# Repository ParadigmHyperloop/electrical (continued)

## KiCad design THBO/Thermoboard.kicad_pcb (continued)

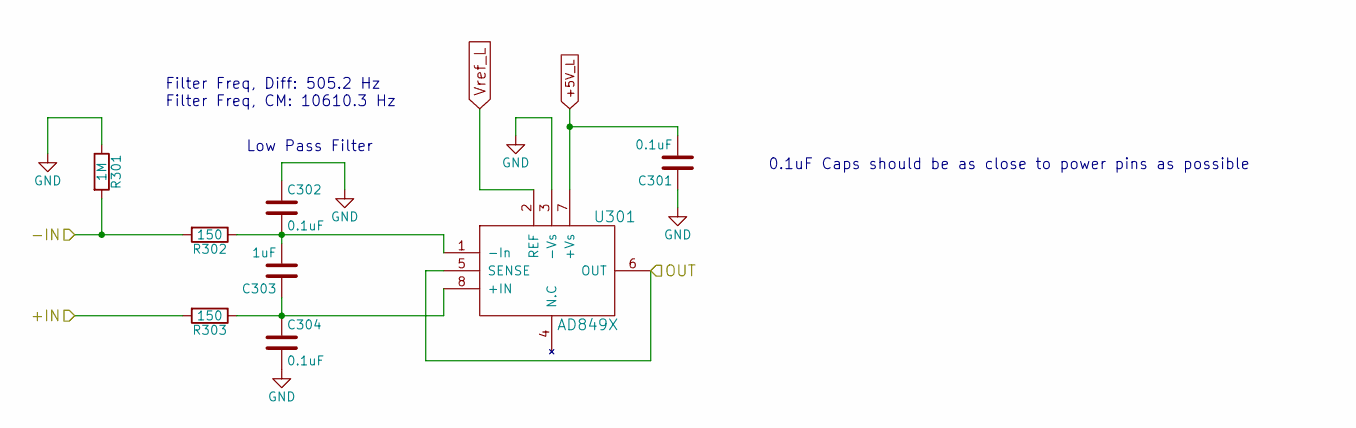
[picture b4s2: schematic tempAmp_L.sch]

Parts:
C201, C202, C204: 0.1uF; C_0603_HandSoldering; Digikey P/N 311-1088-1-ND
C203: 1uF; C_0603_HandSoldering; Digikey P/N 1276-1946-1-ND
R201: 1M; R_0603_HandSoldering; Digikey P/N 311-1.00MHRCT-ND
R202, R203: 150; R_0603_HandSoldering; Digikey P/N 311-150HRCT-ND
U201: AD849X; MSOP-8_3x3mm_Pitch0.65mm; Digikey P/N AD8497ARMZ-ND

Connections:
+5V_L: C201.2, U201.7 (+Vs); also elsewhere on the board
/THERMO_OUPUT_1: U201.5 (SENSE), U201.6 (OUT); also elsewhere on the board
/Thermocouple Amplifier -- 1/+IN: R203.2; also elsewhere on the board
/Thermocouple Amplifier -- 1/-IN: R201.2, R202.2; also elsewhere on the board
GND: C201.1, C202.1, C204.2, R201.1, U201.3 (-Vs); also elsewhere on the board
unnamed: C202.2, C203.2, R202.1, U201.1 (-In)
unnamed: C203.1, C204.1, R203.1, U201.8 (+IN)
Vref_L: U201.2 (REF); also elsewhere on the board

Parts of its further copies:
C301, C302, C304, C401, C402, C404, C501, C502, C504, C601, C602, C604, C701, C702, C704, C801, C802, C804, C901, C902, C904, C1001, C1002, C1004, C1101, C1102, C1104, C1201, C1202, C1204, C1301, C1302, C1304, C1401, C1402, C1404, C1501, C1502, C1504, C1601, C1602, C1604, C1701, C1702, C1704, C1801, C1802, C1804, C1901, C1902, C1904, C2001, C2002, C2004, C2101, C2102, C2104, C2201, C2202, C2204, C2301, C2302, C2304, C2401, C2402, C2404, C2501, C2502, C2504, C2601, C2602, C2604, C2701, C2702, C2704, C2801, C2802, C2804, C2901, C2902, C2904, C3001, C3002, C3004, C3101, C3102, C3104, C3201, C3202, C3204, C3301, C3302, C3304: 0.1uF; C_0603_HandSoldering; Digikey P/N 311-1088-1-ND
C303, C403, C503, C603, C703, C803, C903, C1003, C1103, C1203, C1303, C1403, C1503, C1603, C1703, C1803, C1903, C2003, C2103, C2203, C2303, C2403, C2503, C2603, C2703, C2803, C2903, C3003, C3103, C3203, C3303: 1uF; C_0603_HandSoldering; Digikey P/N 1276-1946-1-ND
R301, R401, R501, R601, R701, R801, R901, R1001, R1101, R1201, R1301, R1401, R1501, R1601, R1701, R1801, R1901, R2001, R2101, R2201, R2301, R2401, R2501, R2601, R2701, R2801, R2901, R3001, R3101, R3201, R3301: 1M; R_0603_HandSoldering; Digikey P/N 311-1.00MHRCT-ND
R302, R303, R402, R403, R502, R503, R602, R603, R702, R703, R802, R803, R902, R903, R1002, R1003, R1102, R1103, R1202, R1203, R1302, R1303, R1402, R1403, R1502, R1503, R1602, R1603, R1702, R1703, R1802, R1803, R1902, R1903, R2002, R2003, R2102, R2103, R2202, R2203, R2302, R2303, R2402, R2403, R2502, R2503, R2602, R2603, R2702, R2703, R2802, R2803, R2902, R2903, R3002, R3003, R3102, R3103, R3202, R3203, R3302, R3303: 150; R_0603_HandSoldering; Digikey P/N 311-150HRCT-ND
U301, U401, U501, U601, U701, U801, U901, U1001, U1101, U1201, U1301, U1401, U1501, U1601, U1701, U1801, U1901, U2001, U2101, U2201, U2301, U2401, U2501, U2601, U2701, U2801, U2901, U3001, U3101, U3201, U3301: AD849X; MSOP-8_3x3mm_Pitch0.65mm; Digikey P/N AD8497ARMZ-ND

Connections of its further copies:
+5V_L: C301.2, C401.2, C501.2, C601.2, C701.2, C801.2, C901.2, C1001.2, C1101.2, C1201.2, C1301.2, C1401.2, C1501.2, C1601.2, C1701.2, U301.7 (+Vs), U401.7 (+Vs), U501.7 (+Vs), U601.7 (+Vs), U701.7 (+Vs), U801.7 (+Vs), U901.7 (+Vs), U1001.7 (+Vs), U1101.7 (+Vs), U1201.7 (+Vs), U1301.7 (+Vs), U1401.7 (+Vs), U1501.7 (+Vs), U1601.7 (+Vs), U1701.7 (+Vs); also elsewhere on the board
+5V_R: C1801.2, C1901.2, C2001.2, C2101.2, C2201.2, C2301.2, C2401.2, C2501.2, C2601.2, C2701.2, C2801.2, C2901.2, C3001.2, C3101.2, C3201.2, C3301.2, U1801.7 (+Vs), U1901.7 (+Vs), U2001.7 (+Vs), U2101.7 (+Vs), U2201.7 (+Vs), U2301.7 (+Vs), U2401.7 (+Vs), U2501.7 (+Vs), U2601.7 (+Vs), U2701.7 (+Vs), U2801.7 (+Vs), U2901.7 (+Vs), U3001.7 (+Vs), U3101.7 (+Vs), U3201.7 (+Vs), U3301.7 (+Vs); also elsewhere on the board
/THERMO_OUPUT_2: U301.5 (SENSE), U301.6 (OUT); also elsewhere on the board
/THERMO_OUPUT_3: U401.5 (SENSE), U401.6 (OUT); also elsewhere on the board
/THERMO_OUPUT_4: U501.5 (SENSE), U501.6 (OUT); also elsewhere on the board
/THERMO_OUPUT_5: U601.5 (SENSE), U601.6 (OUT); also elsewhere on the board
/THERMO_OUPUT_6: U701.5 (SENSE), U701.6 (OUT); also elsewhere on the board
/THERMO_OUPUT_7: U801.5 (SENSE), U801.6 (OUT); also elsewhere on the board
/THERMO_OUPUT_8: U901.5 (SENSE), U901.6 (OUT); also elsewhere on the board
/THERMO_OUPUT_9: U1001.5 (SENSE), U1001.6 (OUT); also elsewhere on the board
/THERMO_OUPUT_10: U1101.5 (SENSE), U1101.6 (OUT); also elsewhere on the board
/THERMO_OUPUT_11: U1201.5 (SENSE), U1201.6 (OUT); also elsewhere on the board
/THERMO_OUPUT_12: U1301.5 (SENSE), U1301.6 (OUT); also elsewhere on the board
/THERMO_OUPUT_13: U1401.5 (SENSE), U1401.6 (OUT); also elsewhere on the board
/THERMO_OUPUT_14: U1501.5 (SENSE), U1501.6 (OUT); also elsewhere on the board
/THERMO_OUPUT_15: U1601.5 (SENSE), U1601.6 (OUT); also elsewhere on the board
/THERMO_OUPUT_16: U1701.5 (SENSE), U1701.6 (OUT); also elsewhere on the board
/THERMO_OUPUT_17: U1801.5 (SENSE), U1801.6 (OUT); also elsewhere on the board
/THERMO_OUPUT_18: U1901.5 (SENSE), U1901.6 (OUT); also elsewhere on the board
/THERMO_OUPUT_19: U2001.5 (SENSE), U2001.6 (OUT); also elsewhere on the board
/THERMO_OUPUT_20: U2101.5 (SENSE), U2101.6 (OUT); also elsewhere on the board
/THERMO_OUPUT_21: U2201.5 (SENSE), U2201.6 (OUT); also elsewhere on the board
/THERMO_OUPUT_22: U2301.5 (SENSE), U2301.6 (OUT); also elsewhere on the board
/THERMO_OUPUT_23: U2401.5 (SENSE), U2401.6 (OUT); also elsewhere on the board
/THERMO_OUPUT_24: U2501.5 (SENSE), U2501.6 (OUT); also elsewhere on the board
/THERMO_OUPUT_25: U2601.5 (SENSE), U2601.6 (OUT); also elsewhere on the board
/THERMO_OUPUT_26: U2701.5 (SENSE), U2701.6 (OUT); also elsewhere on the board
/THERMO_OUPUT_27: U2801.5 (SENSE), U2801.6 (OUT); also elsewhere on the board
/THERMO_OUPUT_28: U2901.5 (SENSE), U2901.6 (OUT); also elsewhere on the board
/THERMO_OUPUT_29: U3001.5 (SENSE), U3001.6 (OUT); also elsewhere on the board
/THERMO_OUPUT_30: U3101.5 (SENSE), U3101.6 (OUT); also elsewhere on the board
/THERMO_OUPUT_31: U3201.5 (SENSE), U3201.6 (OUT); also elsewhere on the board
/THERMO_OUPUT_32: U3301.5 (SENSE), U3301.6 (OUT); also elsewhere on the board
/Thermocouple Amplifier -- 2/+IN: R303.2; also elsewhere on the board
/Thermocouple Amplifier -- 2/-IN: R301.2, R302.2; also elsewhere on the board
/Thermocouple Amplifier -- 3/+IN: R403.2; also elsewhere on the board
/Thermocouple Amplifier -- 3/-IN: R401.2, R402.2; also elsewhere on the board
/Thermocouple Amplifier -- 4/+IN: R503.2; also elsewhere on the board
/Thermocouple Amplifier -- 4/-IN: R501.2, R502.2; also elsewhere on the board
/Thermocouple Amplifier -- 5/+IN: R603.2; also elsewhere on the board
/Thermocouple Amplifier -- 5/-IN: R601.2, R602.2; also elsewhere on the board
/Thermocouple Amplifier -- 6/+IN: R703.2; also elsewhere on the board
/Thermocouple Amplifier -- 6/-IN: R701.2, R702.2; also elsewhere on the board
/Thermocouple Amplifier -- 7/+IN: R803.2; also elsewhere on the board
/Thermocouple Amplifier -- 7/-IN: R801.2, R802.2; also elsewhere on the board
/Thermocouple Amplifier -- 8/+IN: R903.2; also elsewhere on the board
/Thermocouple Amplifier -- 8/-IN: R901.2, R902.2; also elsewhere on the board
/Thermocouple Amplifier -- 9/+IN: R1003.2; also elsewhere on the board
/Thermocouple Amplifier -- 9/-IN: R1001.2, R1002.2; also elsewhere on the board
/Thermocouple Amplifier -- 10/+IN: R1103.2; also elsewhere on the board
/Thermocouple Amplifier -- 10/-IN: R1101.2, R1102.2; also elsewhere on the board
/Thermocouple Amplifier -- 11/+IN: R1203.2; also elsewhere on the board
/Thermocouple Amplifier -- 11/-IN: R1201.2, R1202.2; also elsewhere on the board
/Thermocouple Amplifier -- 12/+IN: R1303.2; also elsewhere on the board
/Thermocouple Amplifier -- 12/-IN: R1301.2, R1302.2; also elsewhere on the board
/Thermocouple Amplifier -- 13/+IN: R1403.2; also elsewhere on the board
/Thermocouple Amplifier -- 13/-IN: R1401.2, R1402.2; also elsewhere on the board
/Thermocouple Amplifier -- 14/+IN: R1503.2; also elsewhere on the board
/Thermocouple Amplifier -- 14/-IN: R1501.2, R1502.2; also elsewhere on the board
/Thermocouple Amplifier -- 15/+IN: R1603.2; also elsewhere on the board
/Thermocouple Amplifier -- 15/-IN: R1601.2, R1602.2; also elsewhere on the board
/Thermocouple Amplifier -- 16/+IN: R1703.2; also elsewhere on the board
/Thermocouple Amplifier -- 16/-IN: R1701.2, R1702.2; also elsewhere on the board
/Thermocouple Amplifier -- 17/+IN: R1803.2; also elsewhere on the board
/Thermocouple Amplifier -- 17/-IN: R1801.2, R1802.2; also elsewhere on the board
/Thermocouple Amplifier -- 18/+IN: R1903.2; also elsewhere on the board
/Thermocouple Amplifier -- 18/-IN: R1901.2, R1902.2; also elsewhere on the board
/Thermocouple Amplifier -- 19/+IN: R2003.2; also elsewhere on the board
/Thermocouple Amplifier -- 19/-IN: R2001.2, R2002.2; also elsewhere on the board
/Thermocouple Amplifier -- 20/+IN: R2103.2; also elsewhere on the board
/Thermocouple Amplifier -- 20/-IN: R2101.2, R2102.2; also elsewhere on the board
/Thermocouple Amplifier -- 21/+IN: R2203.2; also elsewhere on the board
/Thermocouple Amplifier -- 21/-IN: R2201.2, R2202.2; also elsewhere on the board
/Thermocouple Amplifier -- 22/+IN: R2303.2; also elsewhere on the board
/Thermocouple Amplifier -- 22/-IN: R2301.2, R2302.2; also elsewhere on the board
/Thermocouple Amplifier -- 23/+IN: R2403.2; also elsewhere on the board
/Thermocouple Amplifier -- 23/-IN: R2401.2, R2402.2; also elsewhere on the board
/Thermocouple Amplifier -- 24/+IN: R2503.2; also elsewhere on the board
/Thermocouple Amplifier -- 24/-IN: R2501.2, R2502.2; also elsewhere on the board
/Thermocouple Amplifier -- 25/+IN: R2603.2; also elsewhere on the board
/Thermocouple Amplifier -- 25/-IN: R2601.2, R2602.2; also elsewhere on the board
/Thermocouple Amplifier -- 26/+IN: R2703.2; also elsewhere on the board
/Thermocouple Amplifier -- 26/-IN: R2701.2, R2702.2; also elsewhere on the board
/Thermocouple Amplifier -- 27/+IN: R2803.2; also elsewhere on the board
/Thermocouple Amplifier -- 27/-IN: R2801.2, R2802.2; also elsewhere on the board
/Thermocouple Amplifier -- 28/+IN: R2903.2; also elsewhere on the board
/Thermocouple Amplifier -- 28/-IN: R2901.2, R2902.2; also elsewhere on the board
/Thermocouple Amplifier -- 29/+IN: R3003.2; also elsewhere on the board
/Thermocouple Amplifier -- 29/-IN: R3001.2, R3002.2; also elsewhere on the board
/Thermocouple Amplifier -- 30/+IN: R3103.2; also elsewhere on the board
/Thermocouple Amplifier -- 30/-IN: R3101.2, R3102.2; also elsewhere on the board
/Thermocouple Amplifier -- 31/+IN: R3203.2; also elsewhere on the board
/Thermocouple Amplifier -- 31/-IN: R3201.2, R3202.2; also elsewhere on the board
/Thermocouple Amplifier -- 32/+IN: R3303.2; also elsewhere on the board
/Thermocouple Amplifier -- 32/-IN: R3301.2, R3302.2; also elsewhere on the board
GND: C301.1, C302.1, C304.2, C401.1, C402.1, C404.2, C501.1, C502.1, C504.2, C601.1, C602.1, C604.2, C701.1, C702.1, C704.2, C801.1, C802.1, C804.2, C901.1, C902.1, C904.2, C1001.1, C1002.1, C1004.2, C1101.1, C1102.1, C1104.2, C1201.1, C1202.1, C1204.2, C1301.1, C1302.1, C1304.2, C1401.1, C1402.1, C1404.2, C1501.1, C1502.1, C1504.2, C1601.1, C1602.1, C1604.2, C1701.1, C1702.1, C1704.2, C1801.1, C1802.1, C1804.2, C1901.1, C1902.1, C1904.2, C2001.1, C2002.1, C2004.2, C2101.1, C2102.1, C2104.2, C2201.1, C2202.1, C2204.2, C2301.1, C2302.1, C2304.2, C2401.1, C2402.1, C2404.2, C2501.1, C2502.1, C2504.2, C2601.1, C2602.1, C2604.2, C2701.1, C2702.1, C2704.2, C2801.1, C2802.1, C2804.2, C2901.1, C2902.1, C2904.2, C3001.1, C3002.1, C3004.2, C3101.1, C3102.1, C3104.2, C3201.1, C3202.1, C3204.2, C3301.1, C3302.1, C3304.2, R301.1, R401.1, R501.1, R601.1, R701.1, R801.1, R901.1, R1001.1, R1101.1, R1201.1, R1301.1, R1401.1, R1501.1, R1601.1, R1701.1, R1801.1, R1901.1, R2001.1, R2101.1, R2201.1, R2301.1, R2401.1, R2501.1, R2601.1, R2701.1, R2801.1, R2901.1, R3001.1, R3101.1, R3201.1, R3301.1, U301.3 (-Vs), U401.3 (-Vs), U501.3 (-Vs), U601.3 (-Vs), U701.3 (-Vs), U801.3 (-Vs), U901.3 (-Vs), U1001.3 (-Vs), U1101.3 (-Vs), U1201.3 (-Vs), U1301.3 (-Vs), U1401.3 (-Vs), U1501.3 (-Vs), U1601.3 (-Vs), U1701.3 (-Vs), U1801.3 (-Vs), U1901.3 (-Vs), U2001.3 (-Vs), U2101.3 (-Vs), U2201.3 (-Vs), U2301.3 (-Vs), U2401.3 (-Vs), U2501.3 (-Vs), U2601.3 (-Vs), U2701.3 (-Vs), U2801.3 (-Vs), U2901.3 (-Vs), U3001.3 (-Vs), U3101.3 (-Vs), U3201.3 (-Vs), U3301.3 (-Vs); also elsewhere on the board
unnamed: C302.2, C303.2, R302.1, U301.1 (-In)
unnamed: C303.1, C304.1, R303.1, U301.8 (+IN)
unnamed: C402.2, C403.2, R402.1, U401.1 (-In)
unnamed: C403.1, C404.1, R403.1, U401.8 (+IN)
unnamed: C502.2, C503.2, R502.1, U501.1 (-In)
unnamed: C503.1, C504.1, R503.1, U501.8 (+IN)
unnamed: C602.2, C603.2, R602.1, U601.1 (-In)
unnamed: C603.1, C604.1, R603.1, U601.8 (+IN)
unnamed: C702.2, C703.2, R702.1, U701.1 (-In)
unnamed: C703.1, C704.1, R703.1, U701.8 (+IN)
unnamed: C802.2, C803.2, R802.1, U801.1 (-In)
unnamed: C803.1, C804.1, R803.1, U801.8 (+IN)
unnamed: C902.2, C903.2, R902.1, U901.1 (-In)
unnamed: C903.1, C904.1, R903.1, U901.8 (+IN)
unnamed: C1002.2, C1003.2, R1002.1, U1001.1 (-In)
unnamed: C1003.1, C1004.1, R1003.1, U1001.8 (+IN)
unnamed: C1102.2, C1103.2, R1102.1, U1101.1 (-In)
unnamed: C1103.1, C1104.1, R1103.1, U1101.8 (+IN)
unnamed: C1202.2, C1203.2, R1202.1, U1201.1 (-In)
unnamed: C1203.1, C1204.1, R1203.1, U1201.8 (+IN)
unnamed: C1302.2, C1303.2, R1302.1, U1301.1 (-In)
unnamed: C1303.1, C1304.1, R1303.1, U1301.8 (+IN)
unnamed: C1402.2, C1403.2, R1402.1, U1401.1 (-In)
unnamed: C1403.1, C1404.1, R1403.1, U1401.8 (+IN)
unnamed: C1502.2, C1503.2, R1502.1, U1501.1 (-In)
unnamed: C1503.1, C1504.1, R1503.1, U1501.8 (+IN)
unnamed: C1602.2, C1603.2, R1602.1, U1601.1 (-In)
unnamed: C1603.1, C1604.1, R1603.1, U1601.8 (+IN)
unnamed: C1702.2, C1703.2, R1702.1, U1701.1 (-In)
unnamed: C1703.1, C1704.1, R1703.1, U1701.8 (+IN)
unnamed: C1802.2, C1803.2, R1802.1, U1801.1 (-In)
unnamed: C1803.1, C1804.1, R1803.1, U1801.8 (+IN)
unnamed: C1902.2, C1903.2, R1902.1, U1901.1 (-In)
unnamed: C1903.1, C1904.1, R1903.1, U1901.8 (+IN)
unnamed: C2002.2, C2003.2, R2002.1, U2001.1 (-In)
unnamed: C2003.1, C2004.1, R2003.1, U2001.8 (+IN)
unnamed: C2102.2, C2103.2, R2102.1, U2101.1 (-In)
unnamed: C2103.1, C2104.1, R2103.1, U2101.8 (+IN)
unnamed: C2202.2, C2203.2, R2202.1, U2201.1 (-In)
unnamed: C2203.1, C2204.1, R2203.1, U2201.8 (+IN)
unnamed: C2302.2, C2303.2, R2302.1, U2301.1 (-In)
unnamed: C2303.1, C2304.1, R2303.1, U2301.8 (+IN)
unnamed: C2402.2, C2403.2, R2402.1, U2401.1 (-In)
unnamed: C2403.1, C2404.1, R2403.1, U2401.8 (+IN)
unnamed: C2502.2, C2503.2, R2502.1, U2501.1 (-In)
unnamed: C2503.1, C2504.1, R2503.1, U2501.8 (+IN)
unnamed: C2602.2, C2603.2, R2602.1, U2601.1 (-In)
unnamed: C2603.1, C2604.1, R2603.1, U2601.8 (+IN)
unnamed: C2702.2, C2703.2, R2702.1, U2701.1 (-In)
unnamed: C2703.1, C2704.1, R2703.1, U2701.8 (+IN)
unnamed: C2802.2, C2803.2, R2802.1, U2801.1 (-In)
unnamed: C2803.1, C2804.1, R2803.1, U2801.8 (+IN)
unnamed: C2902.2, C2903.2, R2902.1, U2901.1 (-In)
unnamed: C2903.1, C2904.1, R2903.1, U2901.8 (+IN)
unnamed: C3002.2, C3003.2, R3002.1, U3001.1 (-In)
unnamed: C3003.1, C3004.1, R3003.1, U3001.8 (+IN)
unnamed: C3102.2, C3103.2, R3102.1, U3101.1 (-In)
unnamed: C3103.1, C3104.1, R3103.1, U3101.8 (+IN)
unnamed: C3202.2, C3203.2, R3202.1, U3201.1 (-In)
unnamed: C3203.1, C3204.1, R3203.1, U3201.8 (+IN)
unnamed: C3302.2, C3303.2, R3302.1, U3301.1 (-In)
unnamed: C3303.1, C3304.1, R3303.1, U3301.8 (+IN)
Vref_L: U301.2 (REF), U401.2 (REF), U501.2 (REF), U601.2 (REF), U701.2 (REF), U801.2 (REF), U901.2 (REF), U1001.2 (REF), U1101.2 (REF), U1201.2 (REF), U1301.2 (REF), U1401.2 (REF), U1501.2 (REF), U1601.2 (REF), U1701.2 (REF); also elsewhere on the board
Vref_R: U1801.2 (REF), U1901.2 (REF), U2001.2 (REF), U2101.2 (REF), U2201.2 (REF), U2301.2 (REF), U2401.2 (REF), U2501.2 (REF), U2601.2 (REF), U2701.2 (REF), U2801.2 (REF), U2901.2 (REF), U3001.2 (REF), U3101.2 (REF), U3201.2 (REF), U3301.2 (REF); also elsewhere on the board

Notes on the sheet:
Low Pass Filter
0.1uF Caps should be as close to power pins as possible
Filter Freq, Diff: 505.2 Hz Filter Freq, CM: 10610.3 Hz

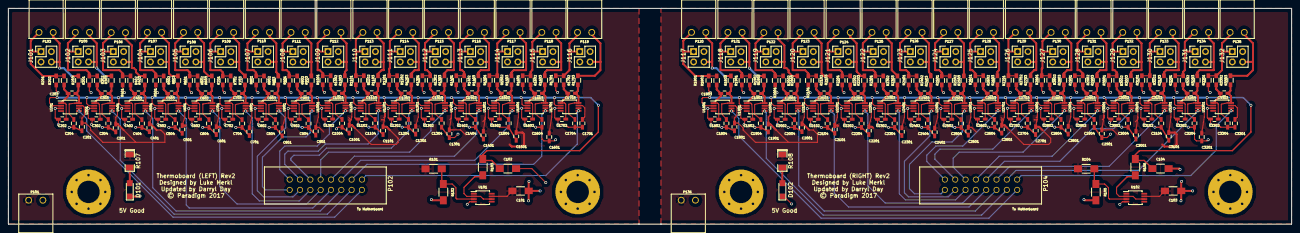
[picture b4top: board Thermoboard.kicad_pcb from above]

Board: 2 copper layers, 315.8 x 53.1 mm, 344 parts (0 on the bottom side), 171 nets.

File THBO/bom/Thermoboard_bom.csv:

Component,Description,Part,References,Value,Footprint,Quantity Per PCB,Datasheet,Digikey P/N,Mfg.,Mfg. P/N
1,Unpolarized capacitor,C,C201 C202 C204 C301 C302 C304 C401 C402 C404 C501 C502 C504 C601 C602 C604 C701 C702 C704 C801 C802 C804 C901 C902 C904 C1001 C1002 C1004 C1101 C1102 C1104 C1201 C1202 C1204 C1301 C1302 C1304 C1401 C1402 C1404 C1501 C1502 C1504 C1601 C1602 C1604 C1701 C1702 C1704 C1801 C1802 C1804 C1901 C1902 C1904 C2001 C2002 C2004 C2101 C2102 C2104 C2201 C2202 C2204 C2301 C2302 C2304 C2401 C2402 C2404 C2501 C2502 C2504 C2601 C2602 C2604 C2701 C2702 C2704 C2801 C2802 C2804 C2901 C2902 C2904 C3001 C3002 C3004 C3101 C3102 C3104 C3201 C3202 C3204 C3301 C3302 C3304,0.1uF,C_0603_HandSoldering,96,,311-1088-1-ND,,
2,Unpolarized capacitor,C,C203 C303 C403 C503 C603 C703 C803 C903 C1003 C1103 C1203 C1303 C1403 C1503 C1603 C1703 C1803 C1903 C2003 C2103 C2203 C2303 C2403 C2503 C2603 C2703 C2803 C2903 C3003 C3103 C3203 C3303,1uF,C_0603_HandSoldering,32,,1276-1946-1-ND,,
3,Unpolarized capacitor,C,C101 C103,1uF,C_1206_HandSoldering,2,,311-1356-1-ND,,
4,Unpolarized capacitor,C,C102 C104,SAT,R_1206_HandSoldering,2,,,,
5,LED generic,LED,D101 D102,GREEN,LED_1206,2,,754-1944-1-ND,Kingbright,APT3216LZGCK
6,Connector/double row/02x02/pin header,CONN_02X02,J101 J102 J103 J104 J105 J106 J107 J108 J109 J110 J111 J112 J113 J114 J115 J116 J117 J118 J119 J120 J121 J122 J123 J124 J125 J126 J127 J128 J129 J130 J131 J132,CONN_02X02,Pin_Header_Straight_2x02_Pitch2.54mm,32,,609-3242-ND,Amphenol FCI,67997-404HLF
7,Connector/single row/01x02/pin header,CONN_01X02,P101 P103 P105 P106 P107 P108 P109 P110 P111 P112 P113 P114 P115 P116 P117 P118 P119 P120 P121 P122 P123 P124 P125 P126 P127 P128 P129 P130 P131 P132 P133 P134 P135 P136,CONN_01X02,phoenix_2pin_3.5mm,34,,277-2416-ND,,
8,Connector/double row/02x08/pin header,CONN_02X08,P102 P104,CONN_02X08,302-S161,2,,ED10523-ND,On Shore Technology Inc.,302-S161
9,Resistor,R,R103 R106,0,R_1206_HandSoldering,2,,749-1062-1-ND,Vishay Dale,RCA06120000Z0EALS
10,Resistor,R,R202 R203 R302 R303 R402 R403 R502 R503 R602 R603 R702 R703 R802 R803 R902 R903 R1002 R1003 R1102 R1103 R1202 R1203 R1302 R1303 R1402 R1403 R1502 R1503 R1602 R1603 R1702 R1703 R1802 R1803 R1902 R1903 R2002 R2003 R2102 R2103 R2202 R2203 R2302 R2303 R2402 R2403 R2502 R2503 R2602 R2603 R2702 R2703 R2802 R2803 R2902 R2903 R3002 R3003 R3102 R3103 R3202 R3203 R3302 R3303,150,R_0603_HandSoldering,64,,311-150HRCT-ND,,
11,Resistor,R,R201 R301 R401 R501 R601 R701 R801 R901 R1001 R1101 R1201 R1301 R1401 R1501 R1601 R1701 R1801 R1901 R2001 R2101 R2201 R2301 R2401 R2501 R2601 R2701 R2801 R2901 R3001 R3101 R3201 R3301,1M,R_0603_HandSoldering,32,,311-1.00MHRCT-ND,,
12,Resistor,R,R102 R105,1k,R_1206_HandSoldering,2,,408-1806-1-ND,Susumu,PRG3216P-1001-D-T5
13,Resistor,R,R107 R108,300,SMD-1206_Pol,2,,P300ALCT-ND,Panasonic,ERJ-P08J301V
14,Resistor,R,R101 R104,3k,R_1206_HandSoldering,2,,408-1910-1-ND,Susumu,HRG3216P-3001-D-T1
15,Thermocouple Amplifiers,AD849X,U201 U301 U401 U501 U601 U701 U801 U901 U1001 U1101 U1201 U1301 U1401 U1501 U1601 U1701 U1801 U1901 U2001 U2101 U2201 U2301 U2401 U2501 U2601 U2701 U2801 U2901 U3001 U3101 U3201 U3301,AD849X,MSOP-8_3x3mm_Pitch0.65mm,32,,AD8497ARMZ-ND,,
16,Transimpedance Amplifier,OPA380,U101 U102,OPA380,MSOP-8_3x3mm_Pitch0.65mm,2,,296-16860-1-ND,,
17,Shunt Jumper,,,,,32,,SAM9042-ND,Samtec Inc.,MNT-102-BK-G
,,,,,,,,,,
,,,,,,,,,,
,,,,,,,,,,
,,,,,,,,,,
,,,,,,,,,,
Component Groups:,17,,,,,,,,,
Component Count:,372,,,,,,,,,
Fitted Components:,372,,,,,,,,,
Number of PCBs:,1,,,,,,,,,
Total components:,372,,,,,,,,,
Schematic Version:,,,,,,,,,,
Schematic Date:,,,,,,,,,,
BoM Date:,6/11/2017 23:30,,,,,,,,,
Schematic Source:,D:/GitHub/full_electrical/THBO/Thermoboard.sch,,,,,,,,,
KiCad Version:,Eeschema 4.0.6,,,,,,,,,
